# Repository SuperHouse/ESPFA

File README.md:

ESPFlasher Adapter
==================

Header adapter that accepts a 1x6 2.54mm ESPFlash header (as used on
the ESPFlasher) and provides matching connections for:

 * 1x6 1.27mm
 * 2x3 2.54mm
 * 2x3 1.27mm

This allows an ESPFlasher to connect to target boards that use these
alternative ESPFlash header formats.

You can view more details at:

  http://www.superhouse.tv/espfa

Credits
-------
 * Jonathan Oxer <jon@oxer.com.au>

License
-------
Copyright 2019-2020 Superhouse Automation Pty Ltd www.superhouse.tv

The hardware portion of this project is licensed under the TAPR Open
Hardware License (www.tapr.org/OHL). The "license" folder within this
repository also contains a copy of this license in plain text format.

The software portion of this project is licensed under the Simplified
BSD License. The "licence" folder within this project contains a capy
of this license in plain text format.

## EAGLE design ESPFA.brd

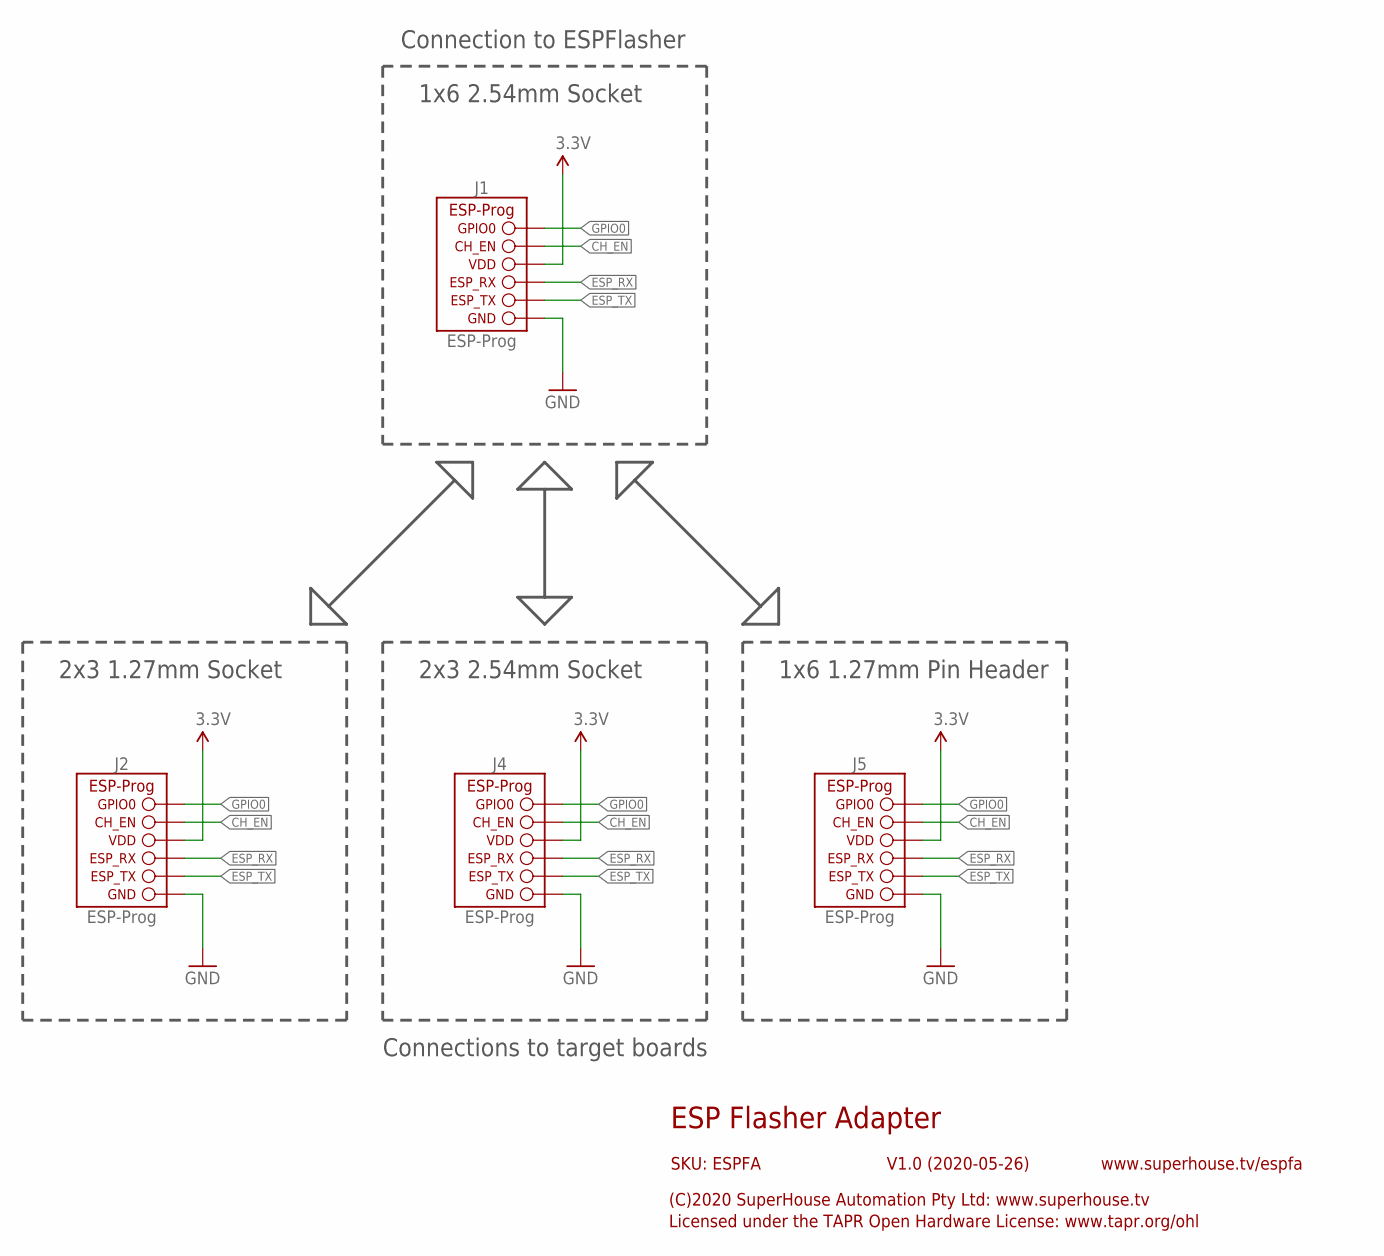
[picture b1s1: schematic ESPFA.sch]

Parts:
J1: ESP-PROG-1X6-2.54-SOCKET-RA; 1X6-2.54-SOCKET-RA
J2: ESP-PROG-2X3-1.27-SHROUDED; 2X3-1.27-SHROUDED
J4: ESP-PROG-2X3-2.54-SHROUDED; 2X3-2.54-SHROUDED
J5: ESP-PROG-1X6-1.27-PINS-RA; 1X6-1.27-PINS-RA

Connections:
3.3V: J1.4 (VDD), J2.2 (VDD), J4.2 (VDD), J5.4 (VDD)
CH_EN: J1.5 (CH_EN), J2.1 (CH_EN), J4.1 (CH_EN), J5.5 (CH_EN)
ESP_RX: J1.3 (ESP_RX), J2.5 (ESP_RX), J4.5 (ESP_RX), J5.3 (ESP_RX)
ESP_TX: J1.2 (ESP_TX), J2.3 (ESP_TX), J4.3 (ESP_TX), J5.2 (ESP_TX)
GND: J1.1 (GND), J2.4 (GND), J4.4 (GND), J5.1 (GND)
GPIO0: J1.6 (GPIO0), J2.6 (GPIO0), J4.6 (GPIO0), J5.6 (GPIO0)

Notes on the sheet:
ESP Flasher Adapter
V1.0 (2020-05-26)
SKU: ESPFA
(C)2020 SuperHouse Automation Pty Ltd: www.superhouse.tv
Licensed under the TAPR Open Hardware License: www.tapr.org/ohl
www.superhouse.tv/espfa
1x6 2.54mm Socket
2x3 1.27mm Socket
2x3 2.54mm Socket
1x6 1.27mm Pin Header
Connection to ESPFlasher
Connections to target boards

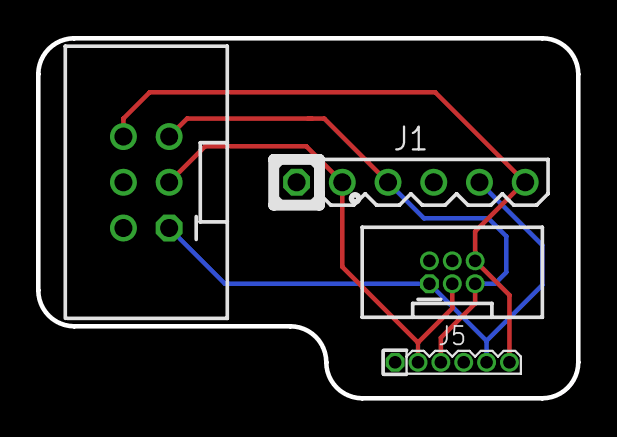
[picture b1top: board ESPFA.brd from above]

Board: 2 copper layers, 30.0 x 20.0 mm, 4 parts (0 on the bottom side), 6 nets.

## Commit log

2020-05-27 Initial project import for v1.0 release
2020-08-13 Restructuring project
2020-09-08 Added image
